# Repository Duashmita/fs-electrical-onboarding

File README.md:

Presentation: https://canva.link/0mz2z3y2d7i3jtd
by Ashmita Dua,
for LV team

## File structure

```
fs-electrical-onboarding/
├── README.md
├── Onboarding Project.pdf            # MAIN PRESENTATION
└── lv/
    ├── Notes.pdf                      # Notes, i.e. process of it all
    ├── Schematics_RSS.pdf             # Exported RSS SCHEMATICS (Important)
    ├── RSS_Circuit_KiCad/             # RSS circuit KiCad project
    │   ├── template.kicad_pro         # Project file (open this)
    │   ├── template.kicad_sch         # Root schematic
    │   ├── template.kicad_pcb  
    │   ├── MCU_RSS.kicad_sch    
    │   ├── Power_RSS.kicad_sch   
    │   ├── RSS.kicad_sym          
    │   ├── RSS.pretty/               
    │   ├── RSS.3dshapes/              
    │   ├── sym-lib-table
    │   ├── fp-lib-table
    │   ├── design-block-lib-table
    │   ├── report.txt
    │   └── meta/                      # Template icon and info
    ├── Resources/
    │   ├── assets/            
    │   ├── Shutdown_VCU.kicad_sch     # Reference shutdown sheet
    │   └── bspd_from_fs4_schematics/  # Reference designs from FS4
    │       ├── BSPD_prototype/        # BSPD schematic + PCB
    │       └── VCU/                   # VCU schematics (MCU, IMU, shutdown)
    └── fs-components/                
        ├── formula_slug_symbol_library.kicad_sym
        ├── formula_slug_footprint_library.pretty/
        ├── formula_slug_design_blocks_library.kicad_blocks/
        ├── 3d_models/
        └── formulaslug_drawing_sheet.kicad_wks
```

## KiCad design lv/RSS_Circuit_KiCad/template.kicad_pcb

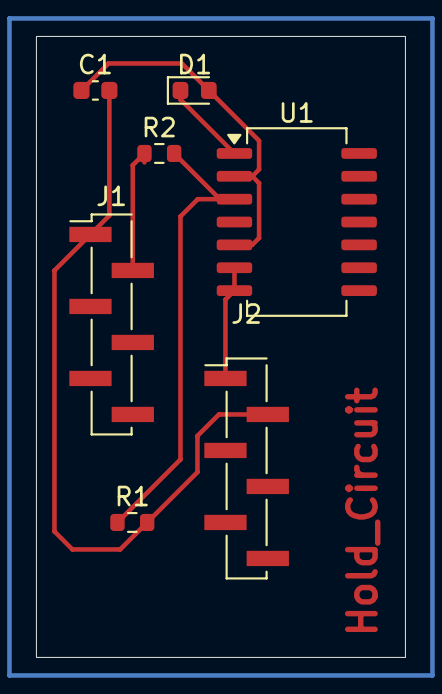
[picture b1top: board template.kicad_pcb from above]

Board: 2 copper layers, 20.5 x 34.5 mm, 7 parts (0 on the bottom side), 6 nets.

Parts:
C1: 10nF; C_0603_1608Metric
D1: D_Small; D_0603_1608Metric
J1: TS_IN; PinHeader_1x06_P2.00mm_Vertical_SMD_Pin1Left
J2: PK_HOLD_Val; PinHeader_1x06_P2.00mm_Vertical_SMD_Pin1Left
R1: 1k; R_0603_1608Metric
R2: 24K; R_0603_1608Metric
U1: MCP6004; SO-14_5.3x10.2mm_P1.27mm

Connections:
/TS+: J1.2, R2.1
GND: C1.2, J1.1, J2.2, R1.2
unnamed: C1.1, D1.2 (A), U1.2 (-), U1.5 (+)
unnamed: D1.1 (K), U1.1
unnamed: J2.1, U1.6 (-), U1.7
unnamed: R1.1, R2.2, U1.3 (+)

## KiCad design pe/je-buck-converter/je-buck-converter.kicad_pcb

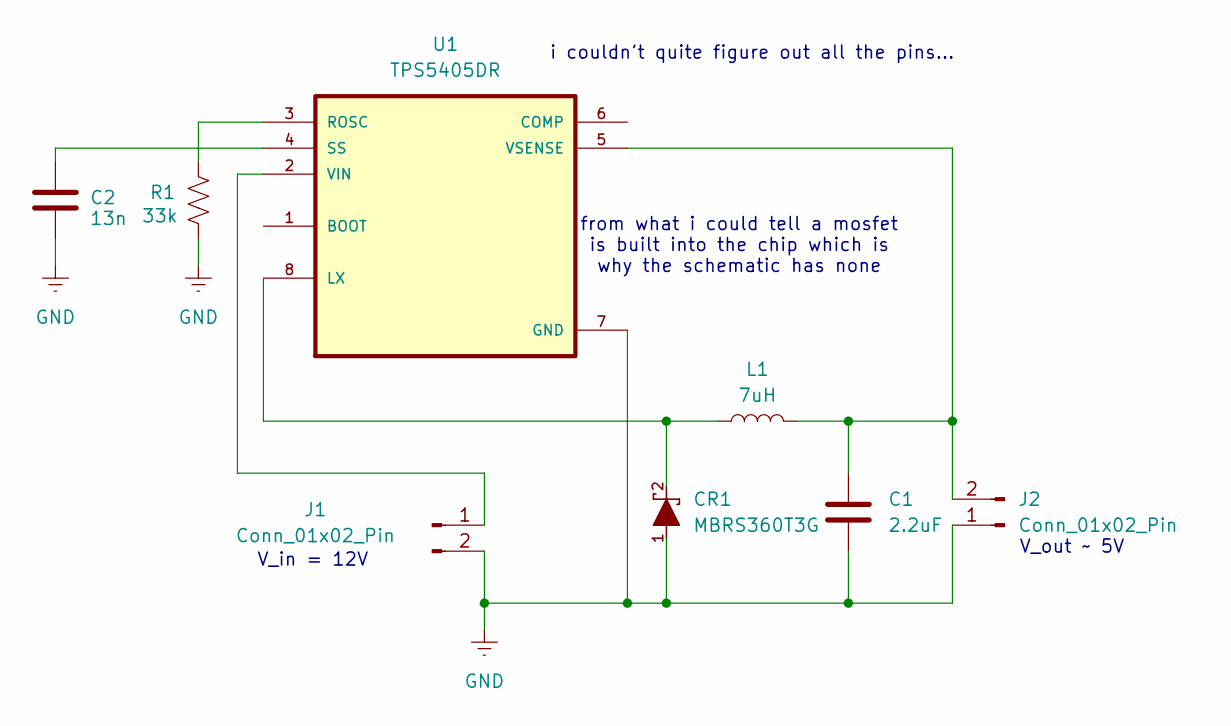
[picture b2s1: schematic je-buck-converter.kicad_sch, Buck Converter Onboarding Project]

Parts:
C1: 2.2uF; C_0201_0603Metric
C2: 13n; C_0201_0603Metric
CR1: MBRS360T3G; DIODE_SMC_7P15X6P25_ONS-M; MANUFACTURER_PART_NUMBER MBRS360T3G
J1, J2: Conn_01x02_Pin; PinSocket_1x02_P2.54mm_Vertical
L1: 7uH; L_Bourns-SRU1028_10.0x10.0mm; Manufacturer Part Number PF0560.702NL
R1: 33k; R_0603_1608Metric
U1: TPS5405DR; SOIC127P599X175-8N

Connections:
GND: C1.2, C2.2, CR1.1, J1.2, J2.1, R1.2, U1.7 (GND)
unnamed: J1.1, U1.2 (VIN)
unnamed: C1.1, J2.2, L1.2, U1.5 (VSENSE)
unnamed: CR1.2, L1.1, U1.8 (LX)
unnamed: R1.1, U1.3 (ROSC)
unnamed: C2.1, U1.4 (SS)

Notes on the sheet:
V_out ~ 5V
from what i could tell a mosfet is built into the chip which is why the schematic has none
i couldn't quite figure out all the pins...
V_in = 12V

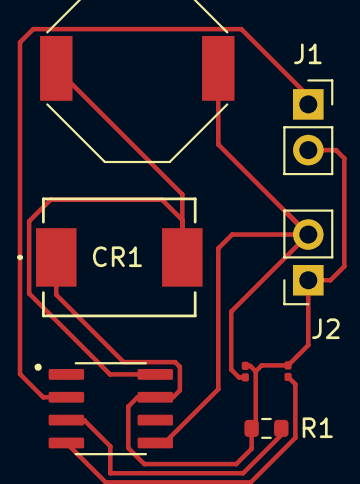
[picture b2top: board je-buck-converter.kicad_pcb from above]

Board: 2 copper layers, 8 parts (0 on the bottom side), 6 nets.

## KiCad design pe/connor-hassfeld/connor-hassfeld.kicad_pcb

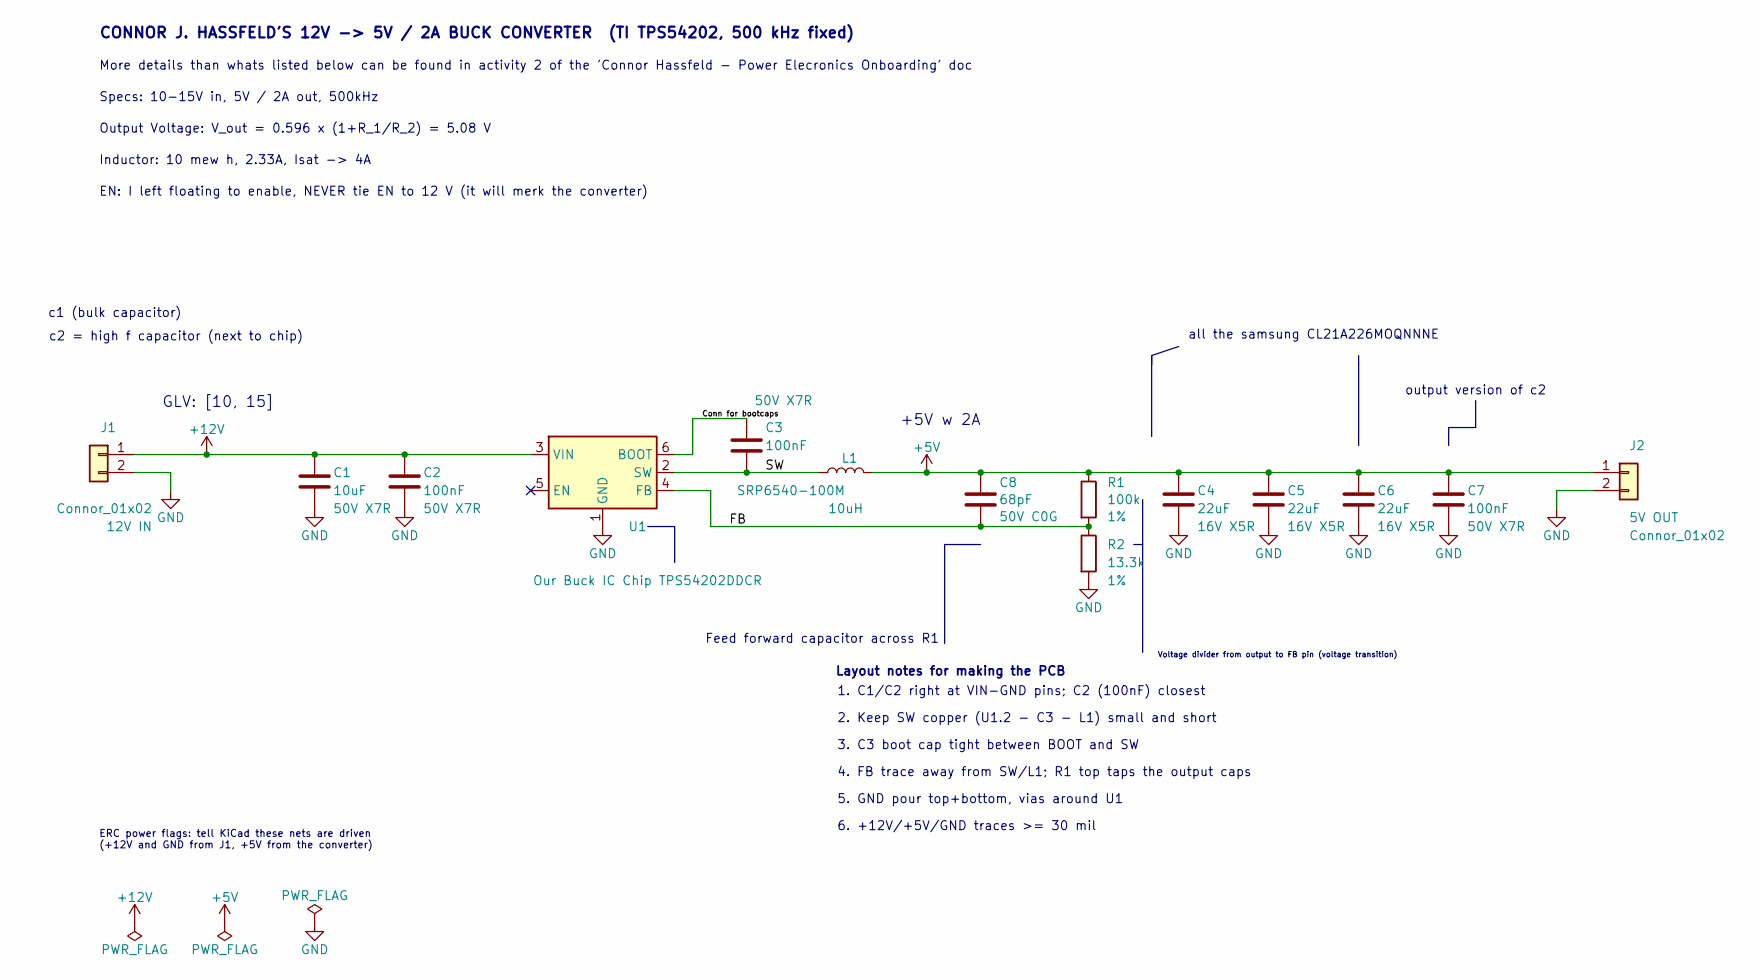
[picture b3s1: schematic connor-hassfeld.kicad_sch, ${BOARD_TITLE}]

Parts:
C1: 10uF; C_1206_3216Metric_Pad1.33x1.80mm_HandSolder; Rating 50V X7R; MFG PN CL31B106KBHNNNE
C2, C3, C7: 100nF; C_0603_1608Metric_Pad1.08x0.95mm_HandSolder; Rating 50V X7R; MFG PN CL10B104KB8NNNC
C4, C5, C6: 22uF; C_0805_2012Metric_Pad1.18x1.45mm_HandSolder; Rating 16V X5R; MFG PN CL21A226MOQNNNE
C8: 68pF; C_0603_1608Metric_Pad1.08x0.95mm_HandSolder; Rating 50V C0G; MFG PN GRM1885C1H680JA01D
J1, J2: Connor_01x02; PinHeader_1x02_P2.54mm_Vertical
L1: SRP6540-100M; L_Bourns_SRP6540; MFG PN SRP6540-100M; Digi PN SRP6540-100MCT-ND
R1: 100k; R_0603_1608Metric_Pad0.98x0.95mm_HandSolder; Rating 1%; MFG PN RC0603FR-07100KL
R2: 13.3k; R_0603_1608Metric_Pad0.98x0.95mm_HandSolder; Rating 1%; MFG PN RC0603FR-0713K3L
U1: Our Buck IC Chip TPS54202DDCR; TSOT-23-6_HandSoldering; MFG PN TPS54202DDCR; Digi PN 296-TPS54202DDCRCT-ND

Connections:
+5V: C4.1, C5.1, C6.1, C7.1, C8.1, J2.1, L1.2, R1.1
+12V: C1.1, C2.1, J1.1, U1.3 (VIN)
/Conn for bootcaps: C3.1, U1.6 (BOOT)
/FB: C8.2, R1.2, R2.1, U1.4 (FB)
/SW: C3.2, L1.1, U1.2 (SW)
GND: C1.2, C2.2, C4.2, C5.2, C6.2, C7.2, J1.2, J2.2, R2.2, U1.1 (GND)

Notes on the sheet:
output version of c2
5. GND pour top+bottom, vias around U1
all the samsung CL21A226MOQNNNE
EN: I left floating to enable, NEVER tie EN to 12 V (it will merk the converter)
c1 (bulk capacitor)
GLV: [10, 15]
Output Voltage: V_out = 0.596 x (1+R_1/R_2) = 5.08 V
ERC power flags: tell KiCad these nets are driven (+12V and GND from J1, +5V from the converter)
+5V w 2A
6. +12V/+5V/GND traces >= 30 mil
Feed forward capacitor across R1
3. C3 boot cap tight between BOOT and SW
1. C1/C2 right at VIN-GND pins; C2 (100nF) closest
Specs: 10-15V in, 5V / 2A out, 500kHz
4. FB trace away from SW/L1; R1 top taps the output caps
Voltage divider from output to FB pin (voltage transition)
Inductor: 10 mew h, 2.33A, Isat -> 4A
c2 = high f capacitor (next to chip)
More details than whats listed below can be found in activity 2 of the 'Connor Hassfeld - Power Elecronics Onboarding' doc
CONNOR J. HASSFELD'S 12V -> 5V / 2A BUCK CONVERTER (TI TPS54202, 500 kHz fixed)
Layout notes for making the PCB
2. Keep SW copper (U1.2 - C3 - L1) small and short

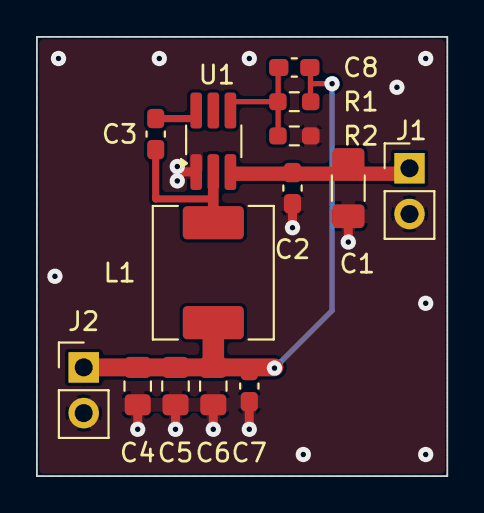
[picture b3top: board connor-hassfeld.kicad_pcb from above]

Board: 2 copper layers, 22.8 x 24.4 mm, 14 parts (0 on the bottom side), 6 nets.

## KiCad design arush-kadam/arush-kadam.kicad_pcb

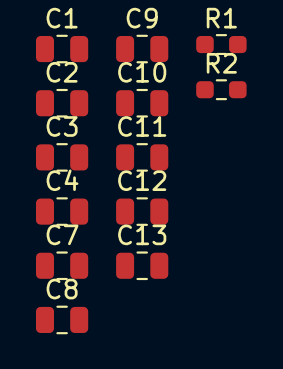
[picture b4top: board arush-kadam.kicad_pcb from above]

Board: 2 copper layers, 13 parts (0 on the bottom side), 4 nets, no tracks yet.

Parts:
C1, C2, C3, C4: 10uF; C_0805_2012Metric
C7, C8, C9, C10, C11, C12, C13: 22uF; C_0805_2012Metric
R1: 158kΩ; R_0603_1608Metric_Pad0.98x0.95mm_HandSolder
R2: 30.1kΩ; R_0603_1608Metric_Pad0.98x0.95mm_HandSolder

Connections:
5V: C7.1, C8.1, C9.1, C10.1, C11.1, C12.1, C13.1, R1.1
15V: C1.1, C2.1, C3.1, C4.1
FB: R1.2, R2.1
GND: C1.2, C2.2, C3.2, C4.2, C7.2, C8.2, C9.2, C10.2, C11.2, C12.2, C13.2, R2.2

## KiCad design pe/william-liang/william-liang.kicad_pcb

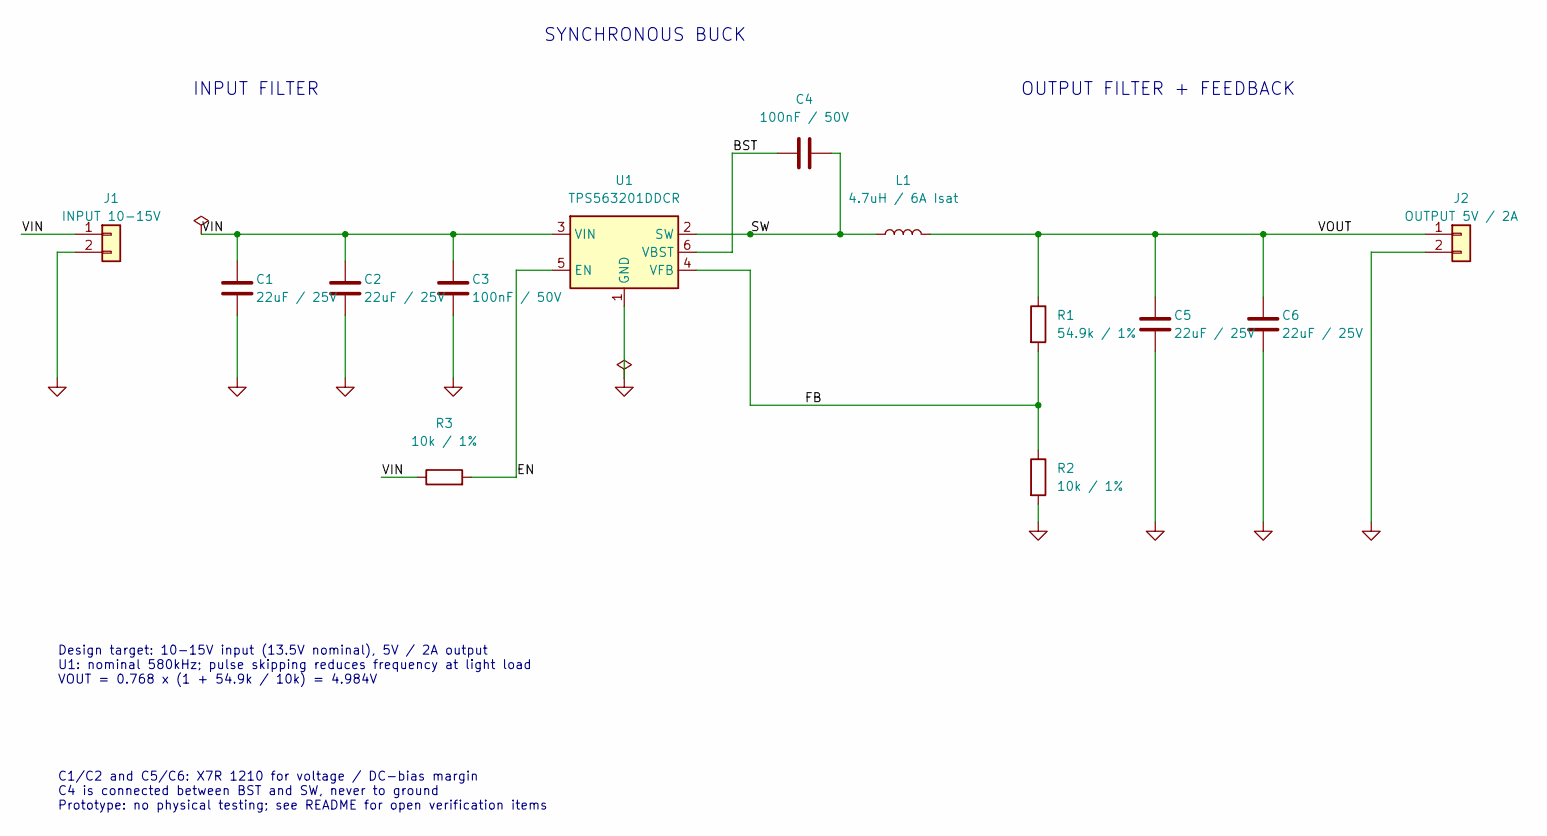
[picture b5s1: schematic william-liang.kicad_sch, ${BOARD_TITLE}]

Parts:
C1, C2, C5, C6: 22uF / 25V; C_1210_3225Metric; MPN C3225X7R1E226M250AB
C3, C4: 100nF / 50V; C_0603_1608Metric; MPN C1608X7R1H104K080AA
J1: INPUT 10-15V; TerminalBlock_Phoenix_MKDS-1,5-2-5.08_1x02_P5.08mm_Horizont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; MPN 1715721
J2: OUTPUT 5V / 2A; TerminalBlock_Phoenix_MKDS-1,5-2-5.08_1x02_P5.08mm_Horizont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; MPN 1715721
L1: 4.7uH / 6A Isat; L_Bourns_SRP5030T; MPN SRP5030TA-4R7M
R1: 54.9k / 1%; R_0603_1608Metric; MPN RC0603FR-0754K9L
R2, R3: 10k / 1%; R_0603_1608Metric; MPN RC0603FR-0710KL
U1: TPS563201DDCR; SOT-23-6; MPN TPS563201DDCR

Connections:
/BST: C4.1, U1.6 (VBST)
/EN: R3.2, U1.5 (EN)
/FB: R1.2, R2.1, U1.4 (VFB)
/SW: C4.2, L1.1, U1.2 (SW)
/VIN: C1.1, C2.1, C3.1, J1.1, R3.1, U1.3 (VIN)
/VOUT: C5.1, C6.1, J2.1, L1.2, R1.1
GND: C1.2, C2.2, C3.2, C5.2, C6.2, J1.2, J2.2, R2.2, U1.1 (GND)

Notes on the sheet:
INPUT FILTER
SYNCHRONOUS BUCK
OUTPUT FILTER + FEEDBACK
Design target: 10-15V input (13.5V nominal), 5V / 2A output U1: nominal 580kHz; pulse skipping reduces frequency at light load VOUT = 0.768 x (1 + 54.9k / 10k) = 4.984V
C1/C2 and C5/C6: X7R 1210 for voltage / DC-bias margin C4 is connected between BST and SW, never to ground Prototype: no physical testing; see README for open verification items

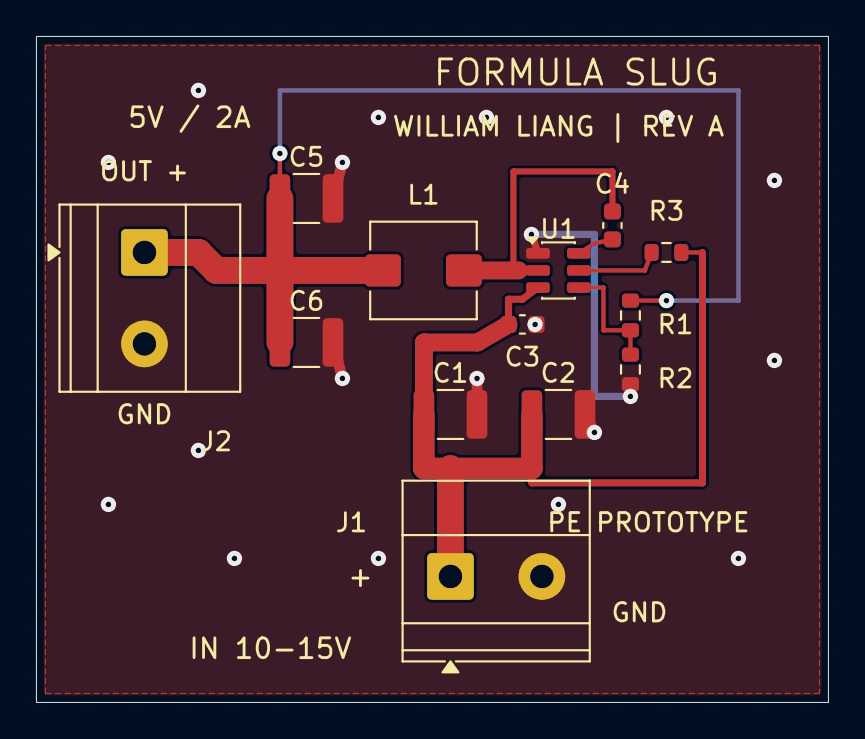
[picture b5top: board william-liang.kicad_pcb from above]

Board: 2 copper layers, 44.0 x 37.0 mm, 13 parts (0 on the bottom side), 7 nets.

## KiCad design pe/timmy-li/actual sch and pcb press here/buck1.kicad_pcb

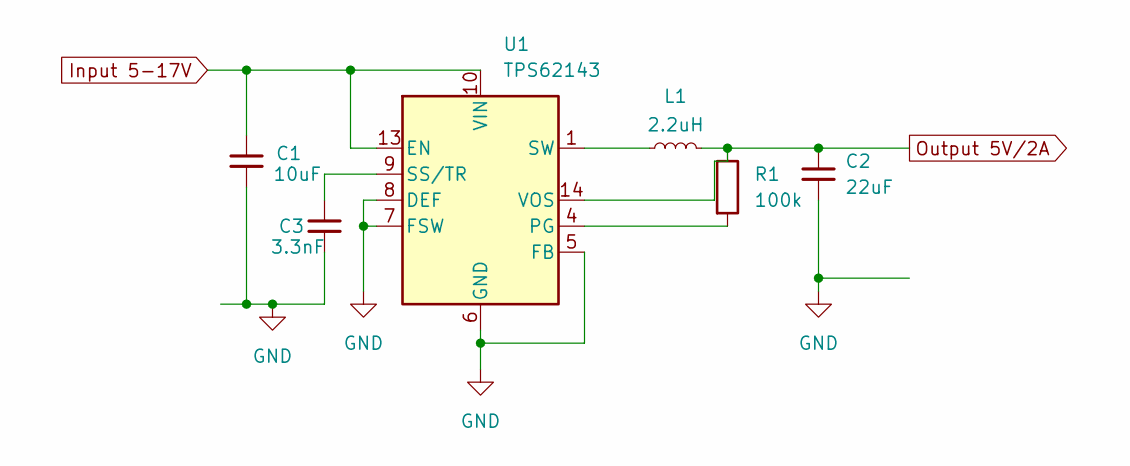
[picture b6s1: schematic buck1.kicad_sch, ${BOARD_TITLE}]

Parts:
C1: 10uF; C_0201_0603Metric_Pad0.64x0.40mm_HandSolder; Manufacturer Part Number CC0603MRX5R8BB106; Digikey Part Number 311-3494-2-ND
C2: 22uF; C_0201_0603Metric_Pad0.64x0.40mm_HandSolder; Manufacturer Part Number MH0603A226M100N8RCZA; Digikey Part Number 6639-MH0603A226M100N8RCZATR-ND
C3: 3.3nF; C_0201_0603Metric_Pad0.64x0.40mm_HandSolder
L1: 2.2uH; L_1210_3225Metric_Pad1.42x2.65mm_HandSolder; Manufacturer Part Number F1C1-322510-2R2M; Digikey Part Number 595-F1C1-322510-2R2MTR-ND
R1: 100k; R_0603_1608Metric
U1: TPS62143; VQFN-16-1EP_3x3mm_P0.5mm_EP1.8x1.8mm_ThermalVias

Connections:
GND: C1.2, C2.2, C3.2, U1.5 (FB), U1.6 (GND), U1.7 (FSW), U1.8 (DEF), U1.15 (GND), U1.16 (GND), U1.17 (GND)
Input 5-17V: C1.1, U1.10 (VIN), U1.11 (VIN), U1.12 (VIN), U1.13 (EN)
unnamed: L1.1, U1.1 (SW), U1.2 (SW), U1.3 (SW)
unnamed: R1.2, U1.4 (PG)
unnamed: C3.1, U1.9 (SS/TR)
Output 5V/2A: C2.1, L1.2, R1.1, U1.14 (VOS)

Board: 2 copper layers, 6 parts (0 on the bottom side), 6 nets, no tracks yet.

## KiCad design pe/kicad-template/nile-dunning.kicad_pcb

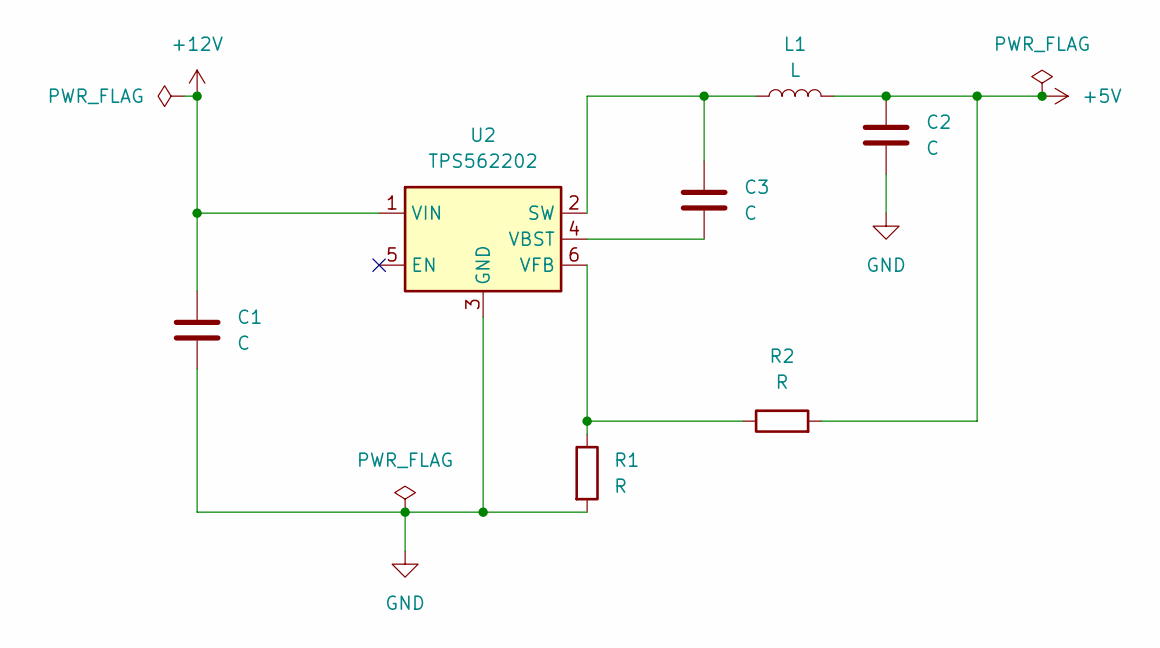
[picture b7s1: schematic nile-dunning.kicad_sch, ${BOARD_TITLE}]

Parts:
C1, C2, C3: C; C_0603_1608Metric
L1: L; IND_TAIYO_NRS4018_TAY
R1, R2: R; R_0402_1005Metric
U2: TPS562202; SOT-563

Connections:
+5V: C2.1, L1.2, R2.2
+12V: C1.1, U2.1 (VIN)
GND: C1.2, C2.2, R1.2, U2.3 (GND)
unnamed: C3.2, L1.1, U2.2 (SW)
unnamed: C3.1, U2.4 (VBST)
unnamed: R1.1, R2.1, U2.6 (VFB)

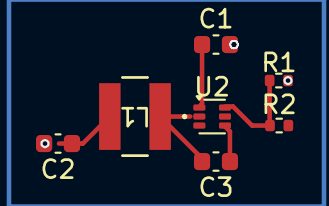
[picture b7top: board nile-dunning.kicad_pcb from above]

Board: 2 copper layers, 7 parts (0 on the bottom side), 6 nets.

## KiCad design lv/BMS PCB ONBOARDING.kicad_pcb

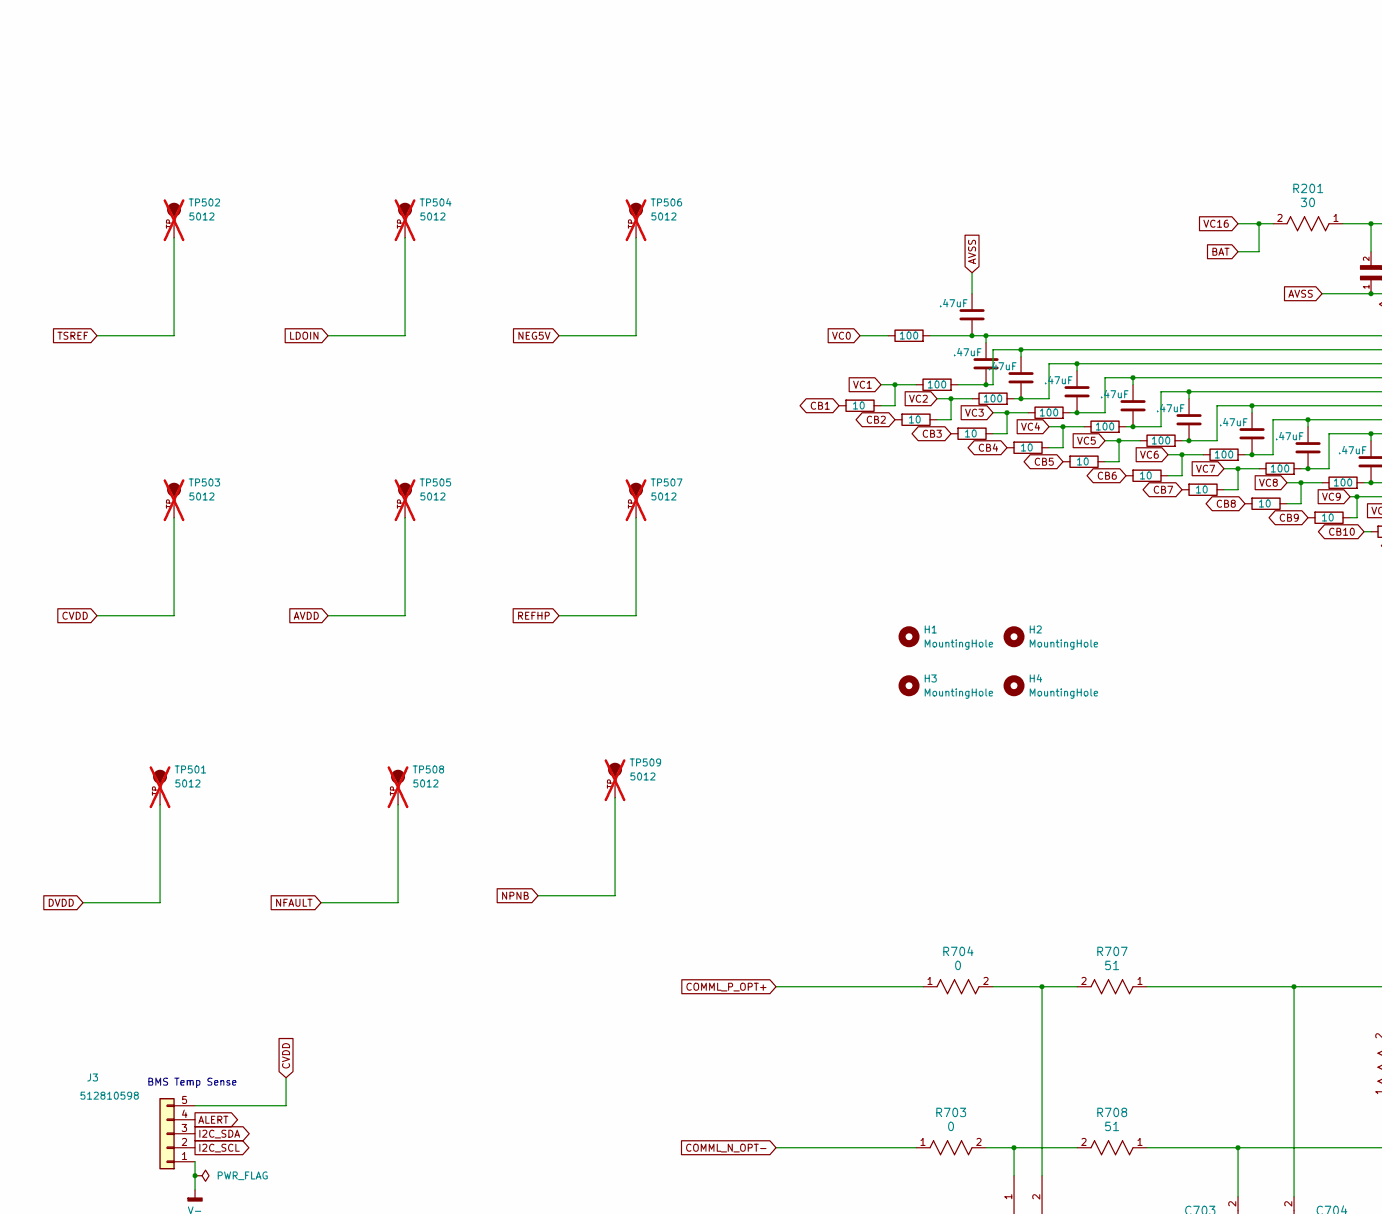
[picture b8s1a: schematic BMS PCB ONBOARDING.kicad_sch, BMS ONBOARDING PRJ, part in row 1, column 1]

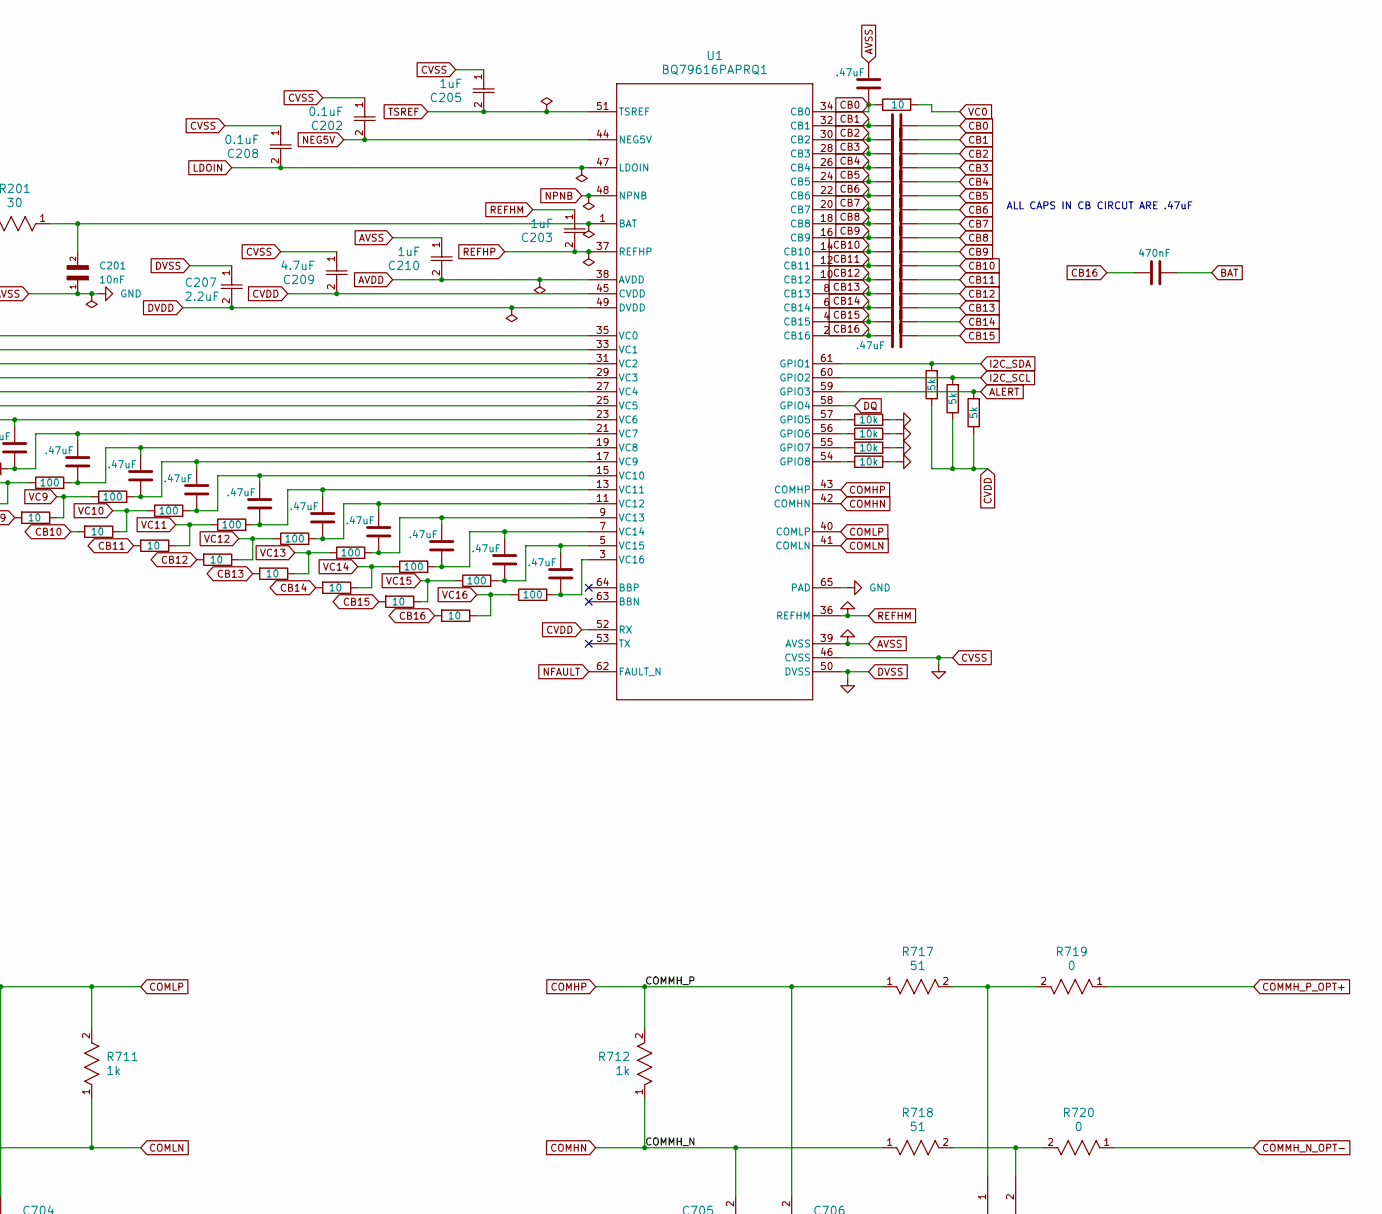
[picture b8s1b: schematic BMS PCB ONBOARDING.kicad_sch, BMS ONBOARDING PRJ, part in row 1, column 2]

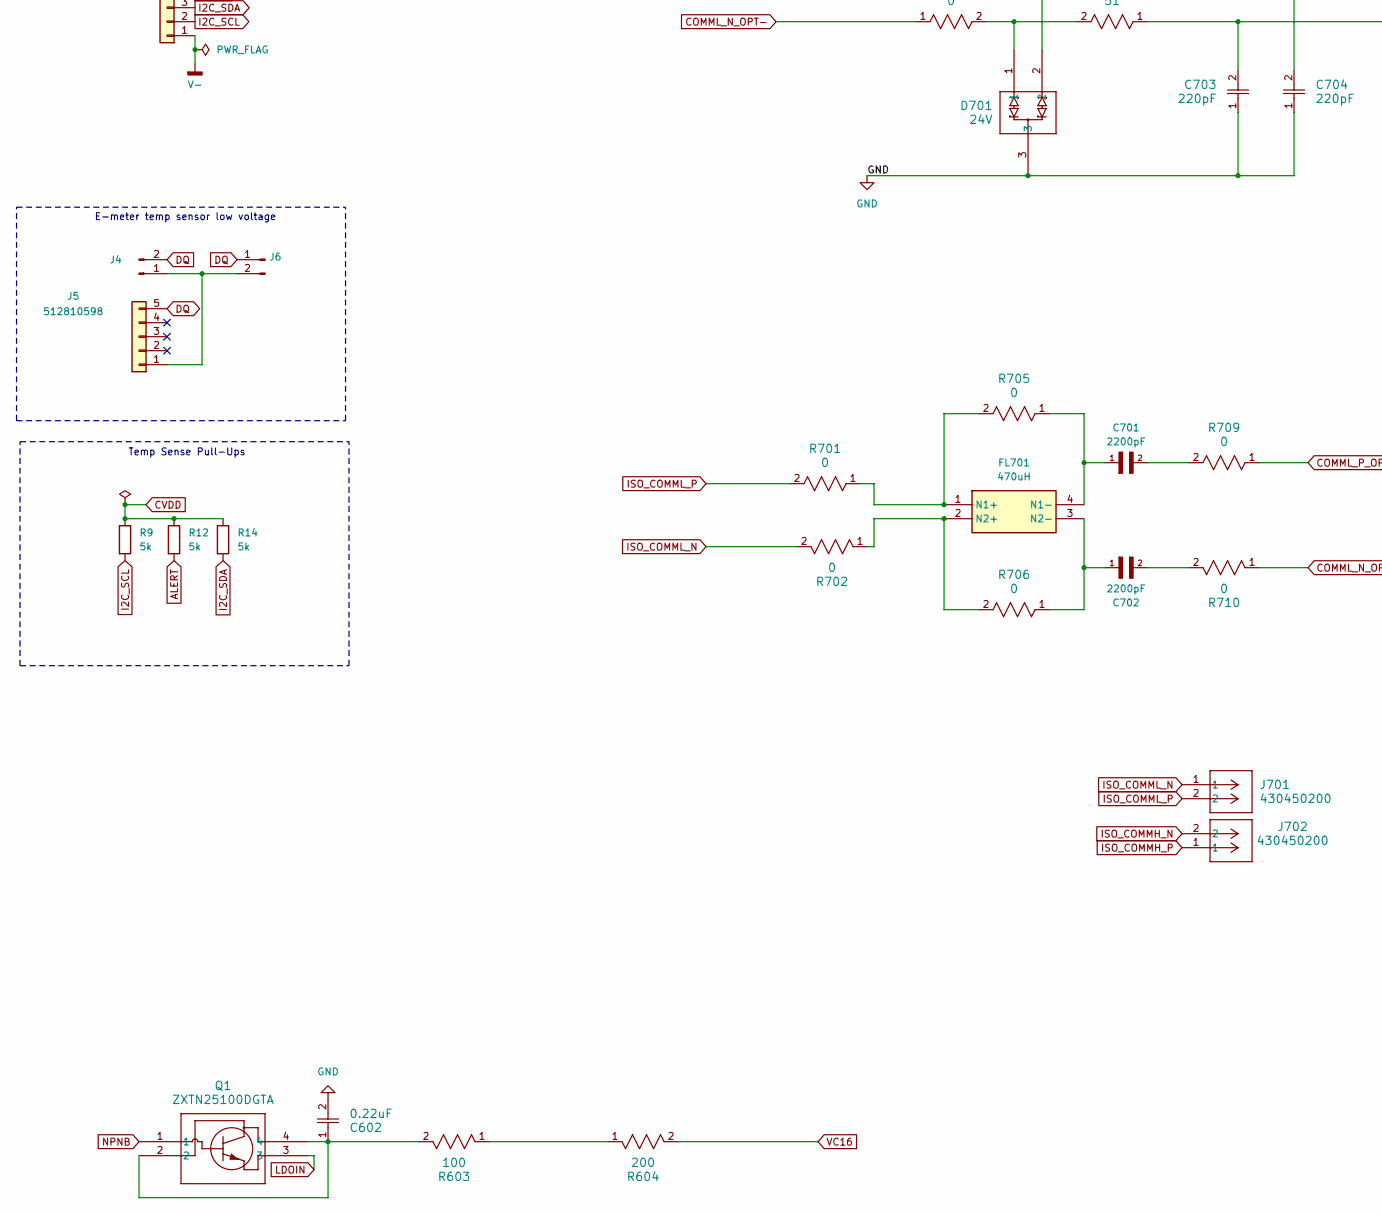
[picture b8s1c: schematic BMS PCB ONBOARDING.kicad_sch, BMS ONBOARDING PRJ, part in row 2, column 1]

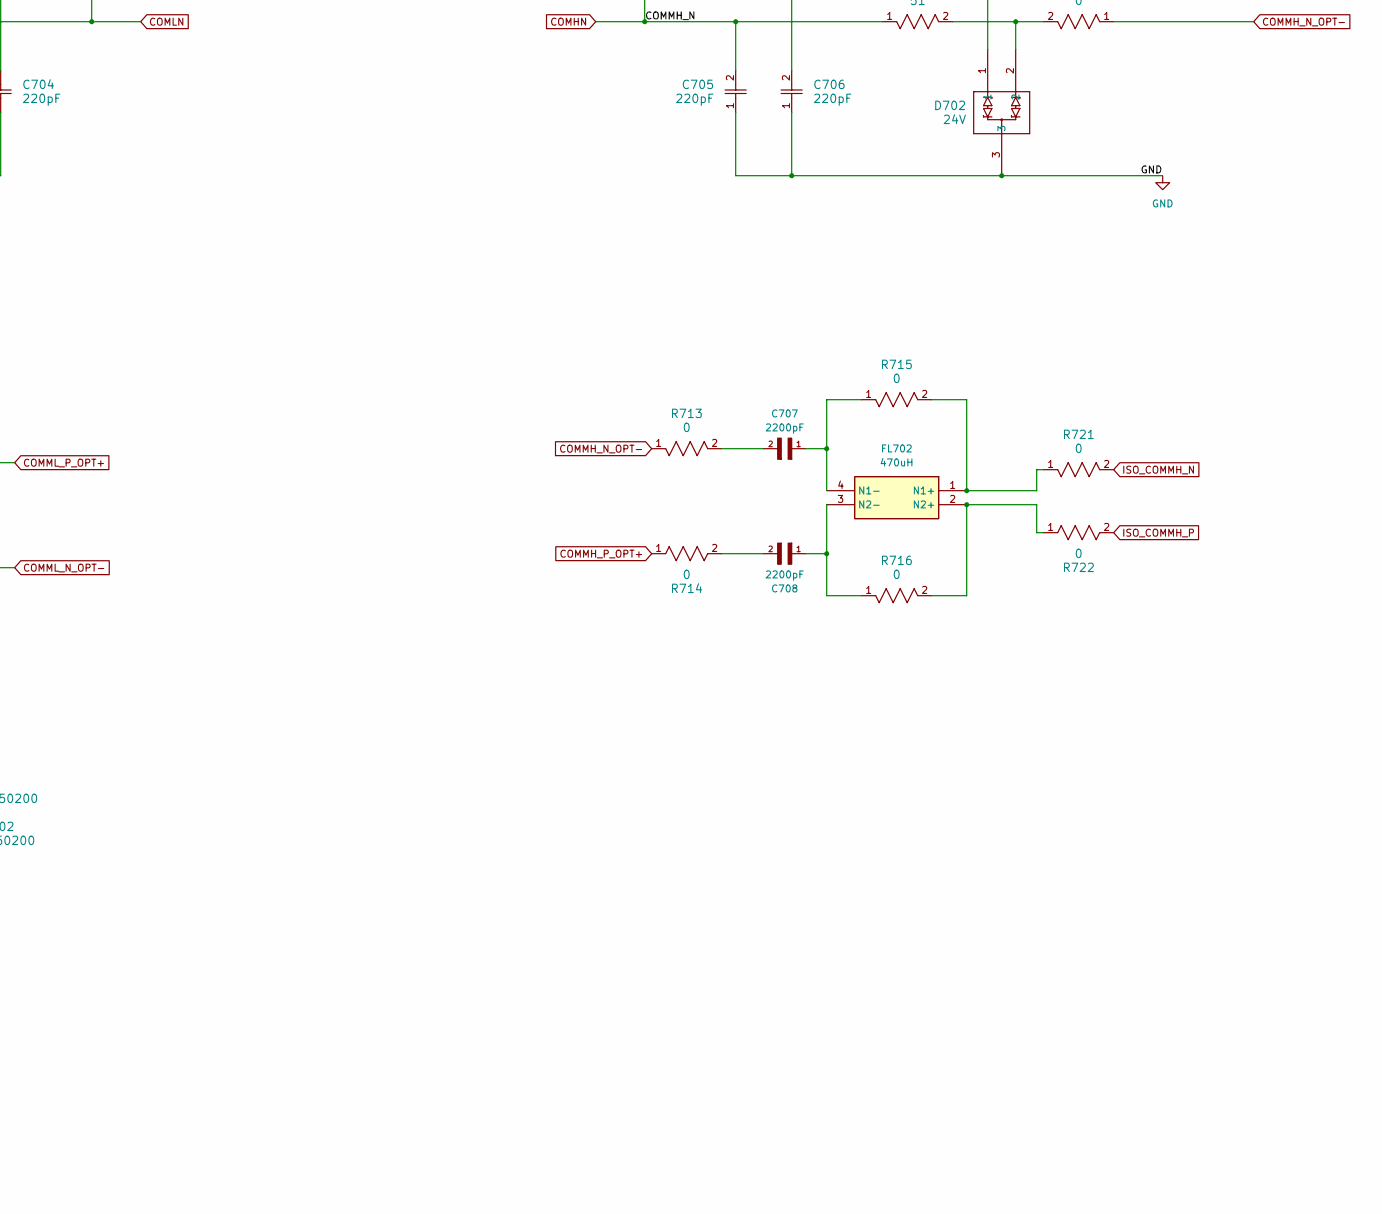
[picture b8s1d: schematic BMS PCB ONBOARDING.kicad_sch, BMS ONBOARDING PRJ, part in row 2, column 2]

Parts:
C1, C2, C3, C4, C5, C6, C7, C8, C9, C10, C11, C12, C19, C20, C21, C22, C23, C24, C25, C26, C27, C28, C29, C30, C31, C32, C33, C34, C35, C36, C37, C38, C39, C40: .47uF; C_0603_1608Metric
C41: 470nF; C_0603_1608Metric
C201: 10nF; CAPC1608X90N; Manufacturer Part Number GCM188R72A103KA37J; JLC PCB Part # C2167085
C202, C208: 0.1uF; CAP_GCM15_1p05X0p55X0p55_MUR-L; Manufacturer Part Number GCM155R71A104KA55D; JLC PCB Part # C161163
C203, C205, C210: 1uF; CAPC18095_95N_KEM-L; Manufacturer Part Number CL10B105KA8NNNC; JLC PCB Part # C29936
C207: 2.2uF; CAPC18095_95N_KEM-L; Manufacturer Part Number CL10B105KA8NNNC; JLC PCB Part # C29936
C209: 4.7uF; CAP_2012_TDK-L; Manufacturer Part Number CC0805KKX7R7BB475; JLC PCB Part # C277499
C602: 0.22uF; G-31_MUR-L; Manufacturer Part Number GCM31MR72A224KA37L; JLC PCB Part # C161277
C701, C702, C707, C708: 2200pF; CAPC3216X160N; Manufacturer Part Number CC1206KKX7RCBB222; JLC PCB Part # C107194
C703, C704, C705, C706: 220pF; CAP_CL10_SAM-L; Manufacturer Part Number CC0603KRX7R9BB221; JLC PCB Part # C107081
D701, D702: 24V; SOT-23; Manufacturer Part Number PESD24VL2BTN; JLC PCB Part # C314266
FL701, FL702: 470uH; 744242471; Mouser Part Number 710-744242471
H1, H2, H3, H4: MountingHole; MountingHole_2.5mm
J3, J5: 512810598; MFG PN 0512810598; Digi PN 900-0512810598CT-ND
J4, J6: 1053131202; Nanofit-1054301202-1x2SMD90Deg; MFG PN 1054301202; Digi PN WM26097CT-ND
J701, J702: 430450200; CON_430450200_MOL
Q1: ZXTN25100DGTA; SOT223_DIO
R1, R2, R3, R4: 10k; R_0805_2012Metric
R5, R7, R8: 5k; R_0805_2012Metric
R9, R12, R14: 5k; R_0805_2012Metric_Pad1.20x1.40mm_HandSolder; MFG PN RC0805FR-134K99L; Digi PN 13-RC0805FR-134K99LCT-ND
R80, R83, R86, R87, R91, R92, R94, R96, R98, R100, R102, R103, R117, R119, R122, R123, R124: 100; R_0805_2012Metric_Pad1.20x1.40mm_HandSolder; MFG PN RC0805FR-134K99L; Digi PN 13-RC0805FR-134K99LCT-ND
R81, R82, R84, R85, R88, R89, R90, R93, R95, R97, R99, R101, R116, R118, R120, R121, R125: 10; R_2512_6332Metric; MFG PN RC0805FR-134K99L; Digi PN 13-RC0805FR-134K99LCT-ND
R201: 30; RC0603N_PAN-L; Manufacturer Part Number ERJ-3EKF30R0V; JLC PCB Part # C403150
R603: 100; RES_CRCW_2010-L; Manufacturer Part Number WF20P1000FTL; JLC PCB Part # C305269
R604: 200; R_2010_5025Metric; Manufacturer Part Number RC2512JK-07200RL; JLC PCB Part # C2935248
R701, R702, R705, R706, R709, R710, R713, R714, R715, R716, R721, R722: 0; RES_CRCW_0805_VIS-L; Manufacturer Part Number CRCW08050000Z0EAHP; JLC PCB Part # C844811
R703, R704, R719, R720: 0; RC0603N_YAG-L; Manufacturer Part Number RC0603JR-070RL; JLC PCB Part # C95177
R707, R708, R717, R718: 51; RC0603N_VIS-L; Manufacturer Part Number CRCW060351R0JNEA; JLC PCB Part # C844178
R711, R712: 1k; RC0603N_PAN-L; Manufacturer Part Number FRC0603F1001TS; JLC PCB Part # C2907002
TP501, TP502, TP503, TP504, TP505, TP506, TP507, TP508, TP509: 5012; TP_5012; PARTREV F; not fitted
U1: BQ79616PAPRQ1; PAP0064F-IPC_A

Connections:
ALERT: J3.4, R5.2, R12.2, U1.59 (GPIO3)
AVDD: C210.2, TP505.TP, U1.38 (AVDD)
AVSS: C21.1, C40.1, C201.1, C202.1, C203.1, C205.1, C207.1, C208.1, C209.1, C210.1, C602.2, C703.1, C704.1, C705.1, C706.1, D701.3, D702.3, R1.2, R2.2, R3.2, R4.2, U1.36 (REFHM), U1.39 (AVSS), U1.46 (CVSS), U1.50 (DVSS), U1.65 (PAD)
BAT: C41.2, R80.1, R81.1, R201.2, R604.2
CB0: C32.2, C40.2, R125.1, U1.34 (CB0)
CB1: C32.1, C33.2, R120.2, U1.32 (CB1)
CB2: C33.1, C34.2, R121.2, U1.30 (CB2)
CB3: C34.1, C35.2, R118.2, U1.28 (CB3)
CB4: C35.1, C36.2, R116.2, U1.26 (CB4)
CB5: C36.1, C37.2, R93.2, U1.24 (CB5)
CB6: C37.1, C38.2, R88.2, U1.22 (CB6)
CB7: C38.1, C39.2, R95.2, U1.20 (CB7)
CB8: C28.2, C39.1, R97.2, U1.18 (CB8)
CB9: C28.1, C29.2, R99.2, U1.16 (CB9)
CB10: C29.1, C30.2, R101.2, U1.14 (CB10)
CB11: C30.1, C31.2, R90.2, U1.12 (CB11)
CB12: C26.2, C31.1, R84.2, U1.10 (CB12)
CB13: C26.1, C27.2, R85.2, U1.8 (CB13)
CB14: C25.2, C27.1, R89.2, U1.6 (CB14)
CB15: C24.2, C25.1, R82.2, U1.4 (CB15)
CB16: C24.1, C41.1, R81.2, U1.2 (CB16)
COMHN: C705.2, R712.1, R718.1, U1.42 (COMHN)
COMHP: C706.2, R712.2, R717.1, U1.43 (COMHP)
COMLN: C703.2, R708.1, R711.1, U1.41 (COMLN)
COMLP: C704.2, R707.1, R711.2, U1.40 (COMLP)
COMMH_N_OPT-: R713.1, R720.1
COMMH_P_OPT+: R714.1, R719.1
COMML_N_OPT-: R703.1, R710.1
COMML_P_OPT+: R704.1, R709.1
CVDD: C209.2, J3.5, R5.1, R7.1, R8.1, R9.1, R12.1, R14.1, TP503.TP, U1.45 (CVDD), U1.52 (RX)
DQ: J4.2, J5.5, J6.1, U1.58 (GPIO4)
DVDD: C207.2, TP501.TP, U1.49 (DVDD)
I2C_SCL: J3.2, R8.2, R9.2, U1.60 (GPIO2)
I2C_SDA: J3.3, R7.2, R14.2, U1.61 (GPIO1)
ISO_COMMH_N: J702.2, R721.2
ISO_COMMH_P: J702.1, R722.2
ISO_COMML_N: J701.1, R702.2
ISO_COMML_P: J701.2, R701.2
LDOIN: C208.2, Q1.3, TP504.TP, U1.47 (LDOIN)
NEG5V: C202.2, TP506.TP, U1.44 (NEG5V)
NFAULT: TP508.TP, U1.62 (FAULT_N)
NPNB: Q1.1, TP509.TP, U1.48 (NPNB)
unnamed: C602.1, Q1.2, Q1.4, R603.2
unnamed: C701.2, R709.2
unnamed: C702.2, R710.2
unnamed: C707.2, R713.2
unnamed: C708.2, R714.2
unnamed: D701.1, R703.2, R708.2
unnamed: D701.2, R704.2, R707.2
unnamed: D702.1, R717.2, R719.2
unnamed: D702.2, R718.2, R720.2
unnamed: FL701.1 (N1+), R701.1, R705.2
unnamed: C701.1, FL701.4 (N1-), R705.1
unnamed: FL701.2 (N2+), R702.1, R706.2
unnamed: C702.1, FL701.3 (N2-), R706.1
unnamed: FL702.1 (N1+), R715.2, R721.1
unnamed: C707.1, FL702.4 (N1-), R715.1
unnamed: FL702.2 (N2+), R716.2, R722.1
unnamed: C708.1, FL702.3 (N2-), R716.1
unnamed: J4.1, J5.1, J6.2
unnamed: R603.1, R604.1
unnamed: C201.2, R201.1, U1.1 (BAT)
unnamed: R3.1, U1.57 (GPIO5)
unnamed: R4.1, U1.56 (GPIO6)
unnamed: R2.1, U1.55 (GPIO7)
unnamed: R1.1, U1.54 (GPIO8)
unnamed: C21.2, C23.1, R124.2, U1.35 (VC0)
unnamed: C22.1, C23.2, R122.2, U1.33 (VC1)
unnamed: C20.1, C22.2, R123.2, U1.31 (VC2)
unnamed: C19.1, C20.2, R119.2, U1.29 (VC3)
unnamed: C8.1, C19.2, R117.2, U1.27 (VC4)
unnamed: C5.1, C8.2, R94.2, U1.25 (VC5)
unnamed: C5.2, C9.1, R96.2, U1.23 (VC6)
unnamed: C9.2, C10.1, R98.2, U1.21 (VC7)
unnamed: C10.2, C11.1, R100.2, U1.19 (VC8)
unnamed: C11.2, C12.1, R102.2, U1.17 (VC9)
unnamed: C7.1, C12.2, R103.2, U1.15 (VC10)
unnamed: C3.1, C7.2, R92.2, U1.13 (VC11)
unnamed: C3.2, C4.1, R86.2, U1.11 (VC12)
unnamed: C4.2, C6.1, R87.2, U1.9 (VC13)
unnamed: C2.1, C6.2, R91.2, U1.7 (VC14)
unnamed: C1.1, C2.2, R83.2, U1.5 (VC15)
unnamed: C1.2, R80.2, U1.3 (VC16)
REFHP: C203.2, TP507.TP, U1.37 (REFHP)
TSREF: C205.2, TP502.TP, U1.51 (TSREF)
V-: J3.1
VC0: R124.1, R125.2
VC1: R120.1, R122.1
VC2: R121.1, R123.1
VC3: R118.1, R119.1
VC4: R116.1, R117.1
VC5: R93.1, R94.1
VC6: R88.1, R96.1
VC7: R95.1, R98.1
VC8: R97.1, R100.1
VC9: R99.1, R102.1
VC10: R101.1, R103.1
VC11: R90.1, R92.1
VC12: R84.1, R86.1
VC13: R85.1, R87.1
VC14: R89.1, R91.1
VC15: R82.1, R83.1

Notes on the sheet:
ALL CAPS IN CB CIRCUT ARE .47uF
E-meter temp sensor low voltage
Temp Sense Pull-Ups
BMS Temp Sense

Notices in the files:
parts and their libraries:
COPYRIGHT: Copyright (C) 2016 Accelerated Designs. All rights reserved
